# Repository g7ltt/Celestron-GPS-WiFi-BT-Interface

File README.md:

# Celestron GPS, WiFi & Bluetooth Interface

My take on Mark Lord's GPS/WiFi/BT interface for Celestron telescope mounts http://rtr.ca/esp32_wifi+bt+gps/

All code is credit to Mark Lord mlord@pobox.com

"For profit" production of this board is expressly forbidden.

Board/schematic files are made with Eagle 9.x.x. PDF file of schematic contains BOM.

Some folks have noted that the ESP32-DevBoard-C as used in this project comes in 2 widths. The V2.0 board now accounts for both widths.

Make sure that you set the voltage from the power PCB to 5.02V BEFORE you add any other PCB's. Failure to set the correct output voltage may result in undesired results and even cause failures of the other parts. Refilling the blue smoke let out by the other components is very nearly impossible for the electronics hobbyist.

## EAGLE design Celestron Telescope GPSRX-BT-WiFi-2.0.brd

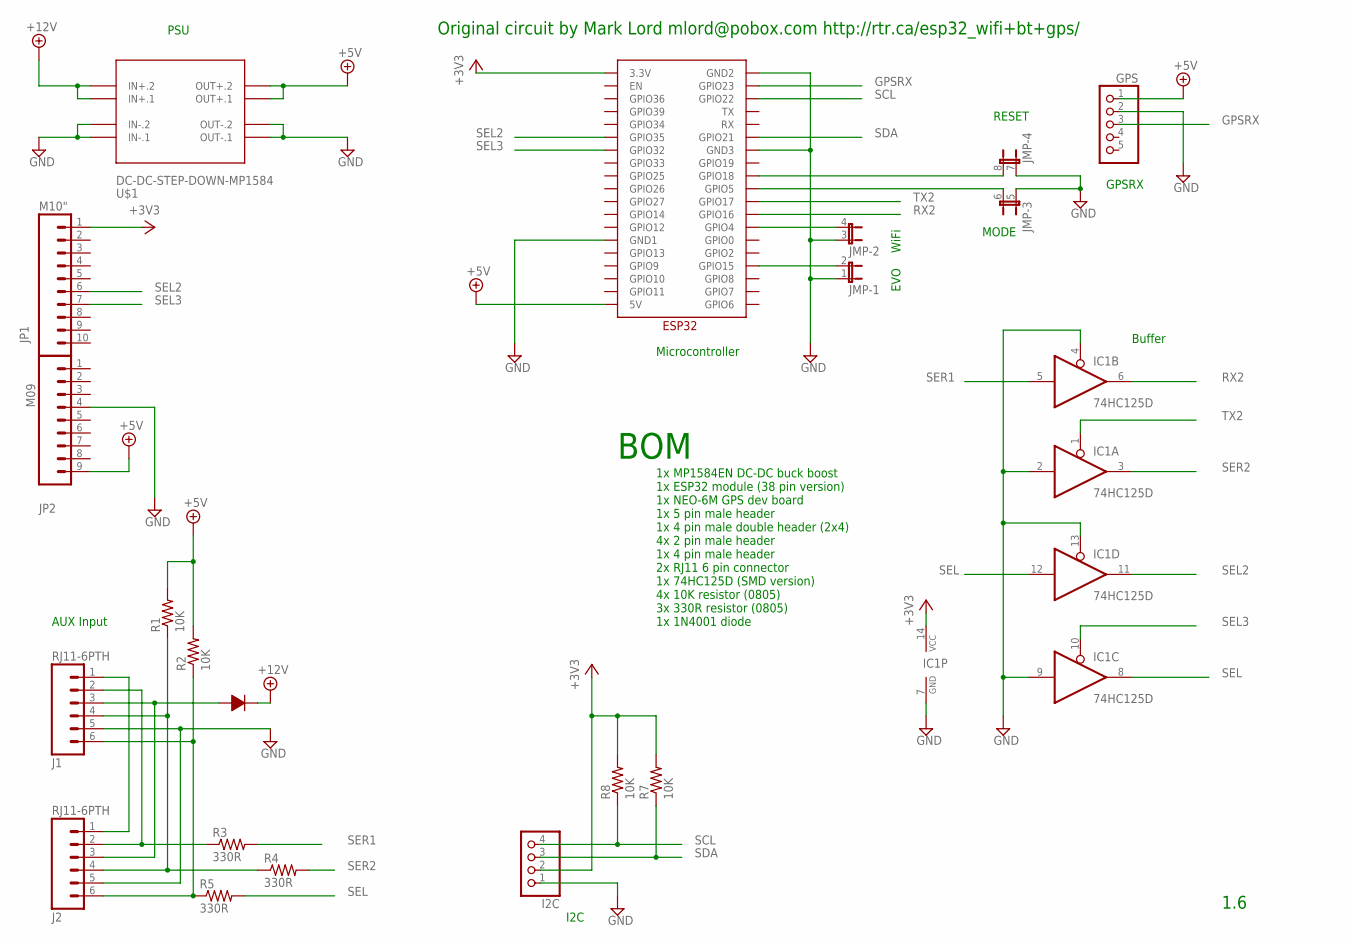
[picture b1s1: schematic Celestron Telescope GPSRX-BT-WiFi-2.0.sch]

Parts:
GPS: PINHD-1X5; 1X05
I2C: PINHD-1X4; 1X04
IC1: 74HC125D; SO14
J1, J2: RJ11-6PTH; RJ11-6
JMP: JP4QE; JP4Q
JP1: M10"; 1X10
JP2: M09; 1X09
R1, R2, R7, R8: 10K; M0805
R3, R4, R5: 330R; M0805
U$1: DC-DC-STEP-DOWN-MP1584
U$2: 1N4001; DIODE-12.70
U$3: ESP32

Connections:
+3V3: I2C.2, IC1.14 (VCC), JP1.1, R7.2, R8.2, U$3.3.3V
+5V: GPS.1, JP2.9, R1.2, R2.2, U$1.OUT+.1, U$1.OUT+.2, U$3.5V
+12V: U$1.IN+.1, U$1.IN+.2, U$2.P$2
EVO: JMP.2, U$3.GPIO15
GND: GPS.2, I2C.1, IC1.2 (I), IC1.4 (OE), IC1.7 (GND), IC1.9 (I), IC1.13 (OE), J1.5, J2.5, JMP.1, JMP.3 (1), JMP.5 (1), JMP.7 (1), JP2.4, U$1.IN-.1, U$1.IN-.2, U$1.OUT-.1, U$1.OUT-.2, U$3.GND1, U$3.GND2, U$3.GND3
GPSRX: GPS.3, U$3.GPIO23
unnamed: J1.6, J2.6, R2.1, R5.1
unnamed: J1.3, J2.3, U$2.P$1
unnamed: J1.4, J2.4, R1.1, R4.1
unnamed: J1.2, J2.2, R3.1
unnamed: J1.1, J2.1
unnamed: JMP.4 (2), U$3.GPIO4
unnamed: JMP.6 (2), U$3.GPIO5
unnamed: JMP.8 (2), U$3.GPIO18
RX2: IC1.6 (O), U$3.GPIO16
SCL: I2C.4, R8.1, U$3.GPIO22
SDA: I2C.3, R7.1, U$3.GPIO21
SEL: IC1.8 (O), IC1.12 (I), R5.2
SEL2: IC1.11 (O), JP1.6, U$3.GPIO35
SEL3: IC1.10 (OE), JP1.7, U$3.GPIO32
SER1: IC1.5 (I), R3.2
SER2: IC1.3 (O), R4.2
TX2: IC1.1 (OE), U$3.GPIO17

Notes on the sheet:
Original circuit by Mark Lord mlord@pobox.com http://rtr.ca/esp32_wifi+bt+gps/
GPSRX
AUX Input
Microcontroller
PSU
Buffer
EVO
WiFi
RESET
MODE
1.6
I2C
BOM
1x MP1584EN DC-DC buck boost 1x ESP32 module (38 pin version) 1x NEO-6M GPS dev board 1x 5 pin male header 1x 4 pin male double header (2x4) 4x 2 pin male header 1x 4 pin male header 2x RJ11 6 pin connector 1x 74HC125D (SMD version) 4x 10K resistor (0805) 3x 330R resistor (0805) 1x 1N4001 diode

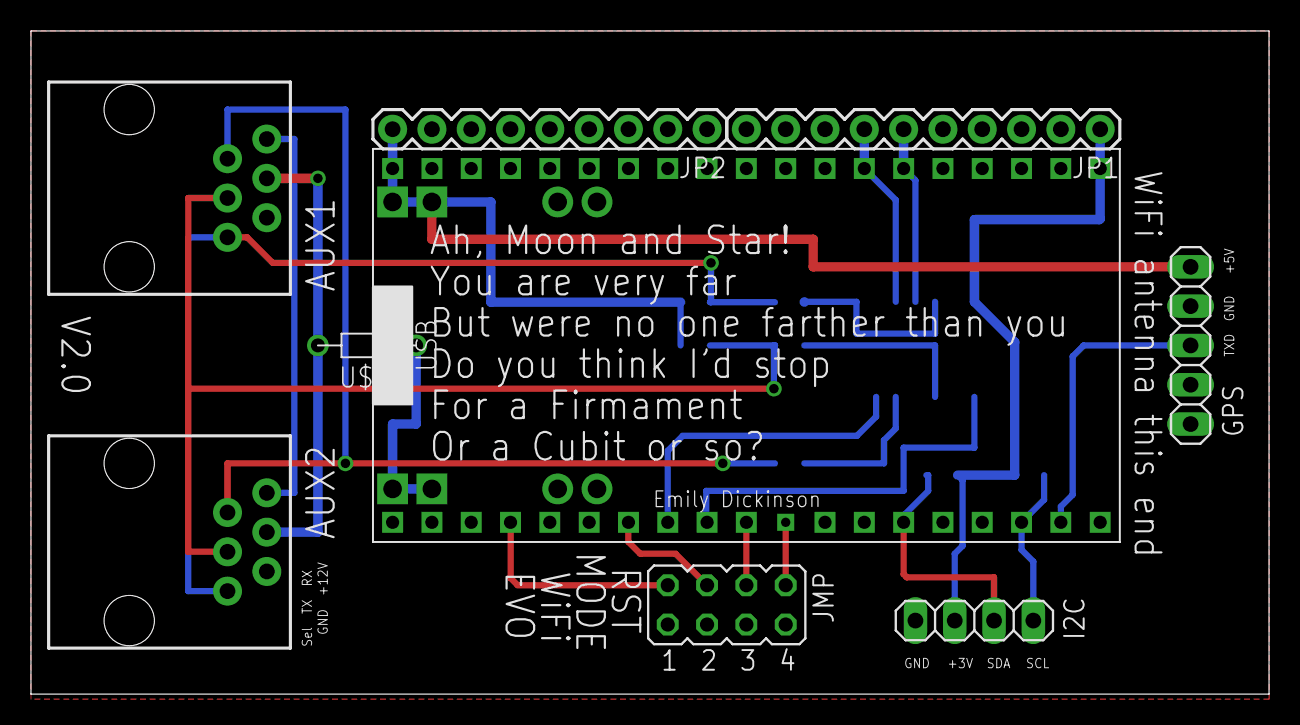
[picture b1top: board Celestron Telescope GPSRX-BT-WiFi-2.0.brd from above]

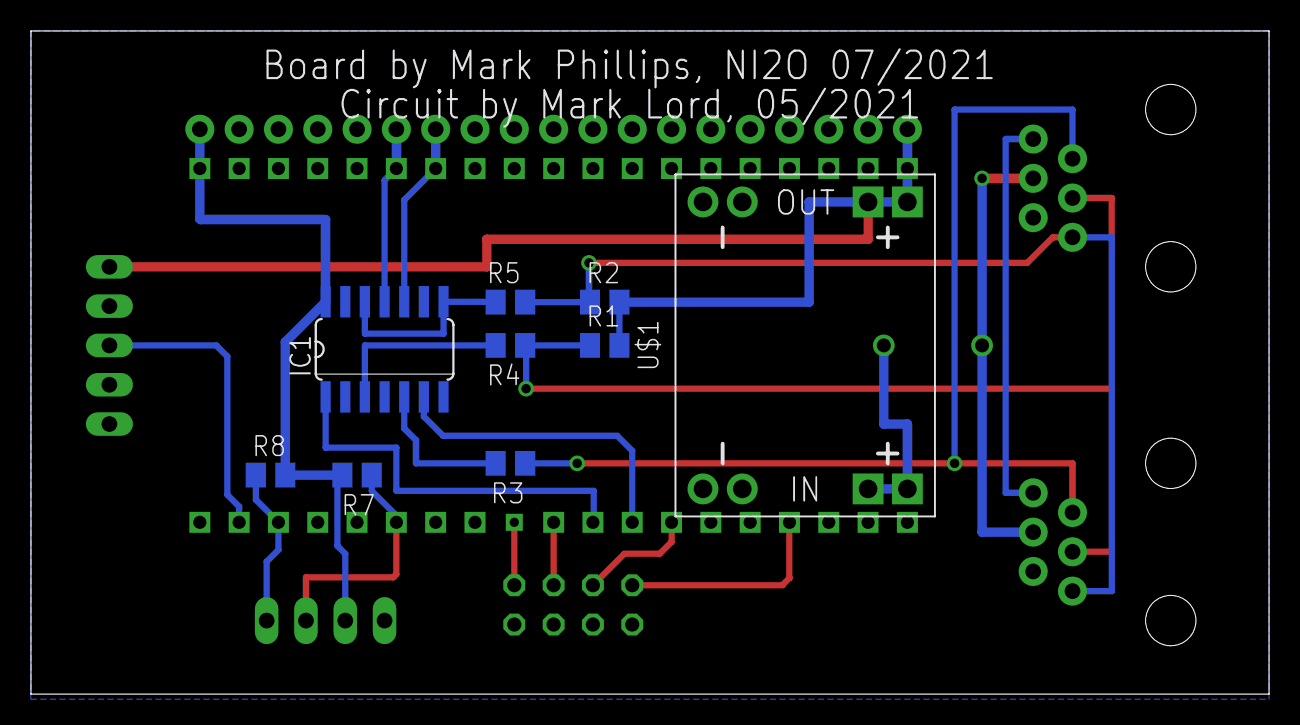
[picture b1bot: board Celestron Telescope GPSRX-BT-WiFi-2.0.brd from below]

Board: 2 copper layers, 80.0 x 42.9 mm, 18 parts (9 on the bottom side), 23 nets.

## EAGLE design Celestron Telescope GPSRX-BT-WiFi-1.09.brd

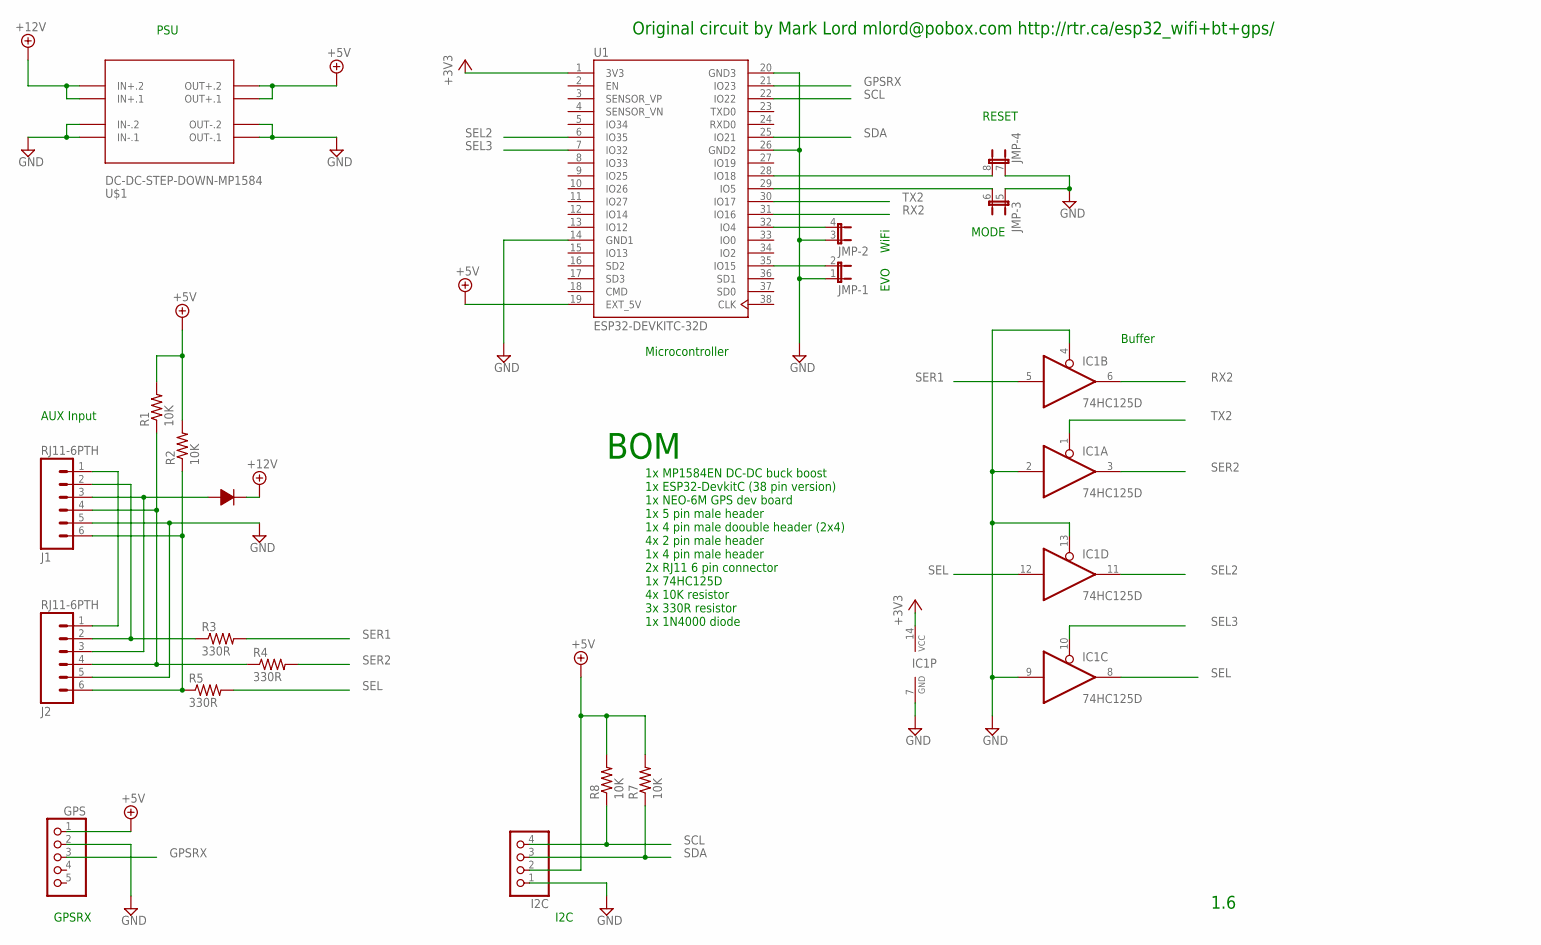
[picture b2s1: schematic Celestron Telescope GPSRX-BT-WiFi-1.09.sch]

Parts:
GPS: PINHD-1X5; 1X05
I2C: PINHD-1X4; 1X04
IC1: 74HC125D; SO14
J1, J2: RJ11-6PTH; RJ11-6
JMP: JP4QE; JP4Q
R1, R2, R7, R8: 10K; M0805
R3, R4, R5: 330R; M0805
U1: ESP32-DEVKITC-32D; MODULE_ESP32-DEVKITC-32D
U$1: DC-DC-STEP-DOWN-MP1584
U$2: 1N4001; DIODE-12.70

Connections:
+3V3: IC1.14 (VCC), U1.1 (3V3)
+5V: GPS.1, I2C.2, R1.2, R2.2, R7.2, R8.2, U1.19 (EXT_5V), U$1.OUT+.1, U$1.OUT+.2
+12V: U$1.IN+.1, U$1.IN+.2, U$2.P$2
EVO: JMP.2, U1.35 (IO15)
GND: GPS.2, I2C.1, IC1.2 (I), IC1.4 (OE), IC1.7 (GND), IC1.9 (I), IC1.13 (OE), J1.5, J2.5, JMP.1, JMP.3 (1), JMP.5 (1), JMP.7 (1), U1.14 (GND1), U1.20 (GND3), U1.26 (GND2), U$1.IN-.1, U$1.IN-.2, U$1.OUT-.1, U$1.OUT-.2
GPSRX: GPS.3, U1.21 (IO23)
unnamed: J1.6, J2.6, R2.1, R5.1
unnamed: J1.3, J2.3, U$2.P$1
unnamed: J1.4, J2.4, R1.1, R4.1
unnamed: J1.2, J2.2, R3.1
unnamed: J1.1, J2.1
unnamed: JMP.4 (2), U1.32 (IO4)
unnamed: JMP.6 (2), U1.29 (IO5)
unnamed: JMP.8 (2), U1.28 (IO18)
RX2: IC1.6 (O), U1.31 (IO16)
SCL: I2C.4, R8.1, U1.22 (IO22)
SDA: I2C.3, R7.1, U1.25 (IO21)
SEL: IC1.8 (O), IC1.12 (I), R5.2
SEL2: IC1.11 (O), U1.6 (IO35)
SEL3: IC1.10 (OE), U1.7 (IO32)
SER1: IC1.5 (I), R3.2
SER2: IC1.3 (O), R4.2
TX2: IC1.1 (OE), U1.30 (IO17)

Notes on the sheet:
Original circuit by Mark Lord mlord@pobox.com http://rtr.ca/esp32_wifi+bt+gps/
GPSRX
AUX Input
Microcontroller
PSU
Buffer
EVO
WiFi
RESET
MODE
1.6
I2C
BOM
1x MP1584EN DC-DC buck boost 1x ESP32-DevkitC (38 pin version) 1x NEO-6M GPS dev board 1x 5 pin male header 1x 4 pin male doouble header (2x4) 4x 2 pin male header 1x 4 pin male header 2x RJ11 6 pin connector 1x 74HC125D 4x 10K resistor 3x 330R resistor 1x 1N4000 diode

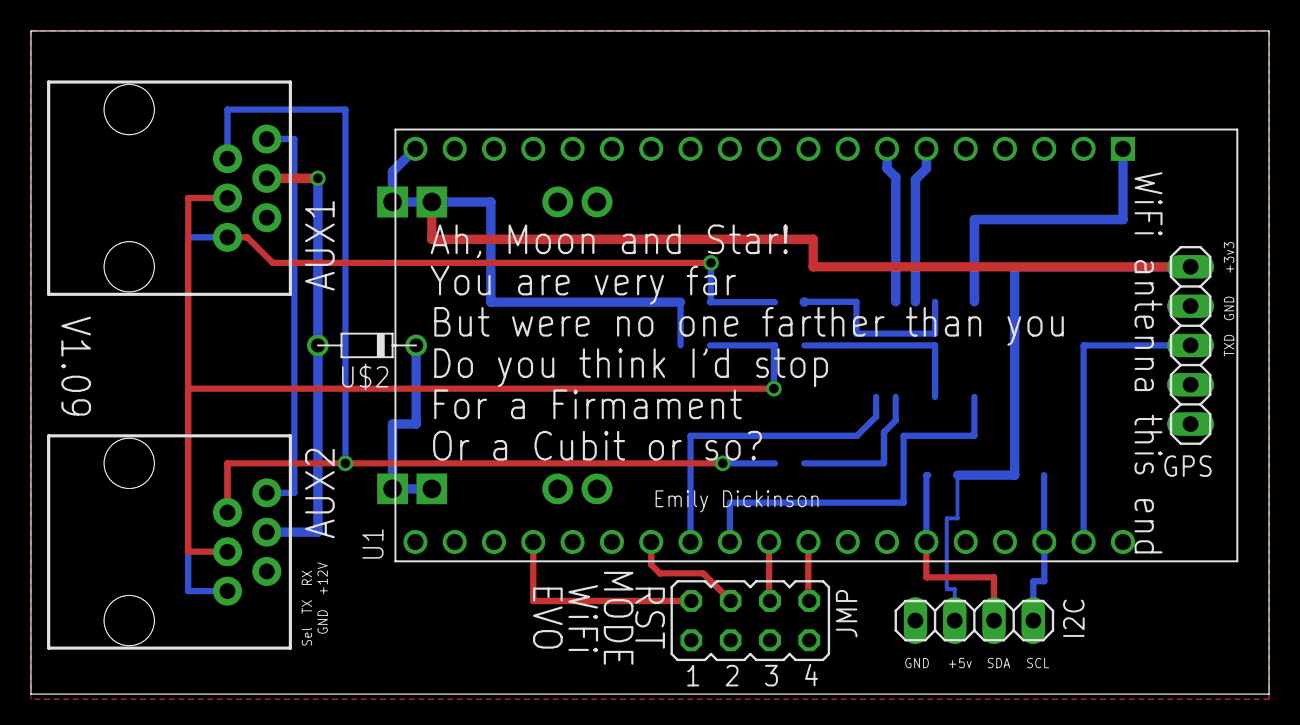
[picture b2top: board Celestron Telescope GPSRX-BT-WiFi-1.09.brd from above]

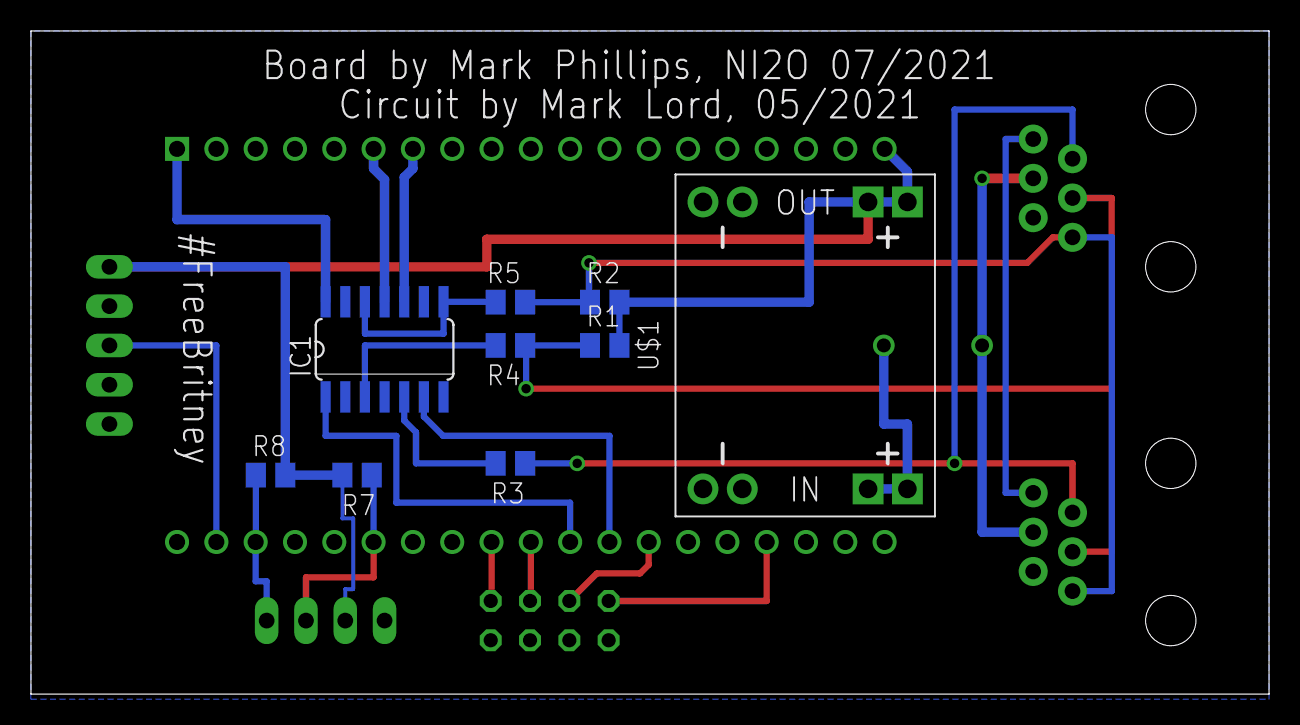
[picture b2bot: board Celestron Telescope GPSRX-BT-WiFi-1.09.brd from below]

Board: 2 copper layers, 80.0 x 42.9 mm, 16 parts (9 on the bottom side), 23 nets.

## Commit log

2021-08-10 Add files via upload
    Circuit diagram and BOM

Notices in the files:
parts and their libraries:
SparkFun: Licensing: CC v3.0 Share-Alike You are welcome to use this library for commercial purposes.
diy-modules: Released under the Creative Commons Attribution 4.0 International License: http://creativecommons.org/licenses/by/4.0
